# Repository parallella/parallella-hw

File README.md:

PARALLELLA: Supercomputing for Everyone
========================================	

This repository contains open source board and FPGA designs associated with the Parallella project. 

## Directory

Board                                | Description                | CAD       | Status     |
-------------------------------------|----------------------------|-----------|------------|
[parallella](parallella/README.md)   | Parallella                 | Cadence   | Production |
[porcupine](porcupine/README.md)     | Parallella Breakout Board  | KiCad     | Production |
[meta](meta)                         | Epiphany 4096-core System  | Cadence   | Prototype  |
[buddy](buddy)                       | Epiphany-V Evaluation Board| Cadence   | Prototype  |
[paracase](paracase)                 | Aluminum Case              | SolidWorks| Production |
[parasdr](parasdr/README.md)         | SDR adapter Board          | Cadence   | Production |
[kvision](kvision/README.md)         | Stereo Vision Board        | Altium    | Prototype  |
[paralime](paralime)                 | Myriad-RF daughter Board   | KiCad     | Prototype  |
[paracluster](paracluster/README.md) | Cluster Board              | N/A       | Prototype  |
[paralib](paralib)                   | CAD librares               | Various   | Prouction  |
[paratemplate](paratemplate)         | Daugher Card Template      | KiCad     | Production |
[paratile](paratile/README.md)       | Breakout Board             | Eagle     | Prototype  |
[aafm](aafm/README.md)               | Epiphany-III FMC Board     | KiCad     | Production |
[archive](archive)                   | Old Parallella stuff       | N/A       | Obsolete   |

## FPGA Design Sources
All Parallella related FPGA sources have been moved to the [OH! library](https://github.com/parallella/oh) library and released under MIT license.

## License
Board design files are released under the Creative Common Share Alike license unlesss otherwise specified.

## How to do a pull-request

1. Fork this repository to your personal github account using the 'fork' button 2. above
3. Clone your 'parallella-hw' fork to a local computer using 'git clone'
4. Create a new sub-directory at the root of the repo
5. Add your project files with the appropriate license clearly stated
6. Add a README.md file (see the skeleton directory for a template)
7. Use git add-->git commit-->git push to add changes to your fork of 'parallella-examples'
8. Submit a pull request by clicking the 'pull request' button on YOUR github 'parallella-examples' repo.

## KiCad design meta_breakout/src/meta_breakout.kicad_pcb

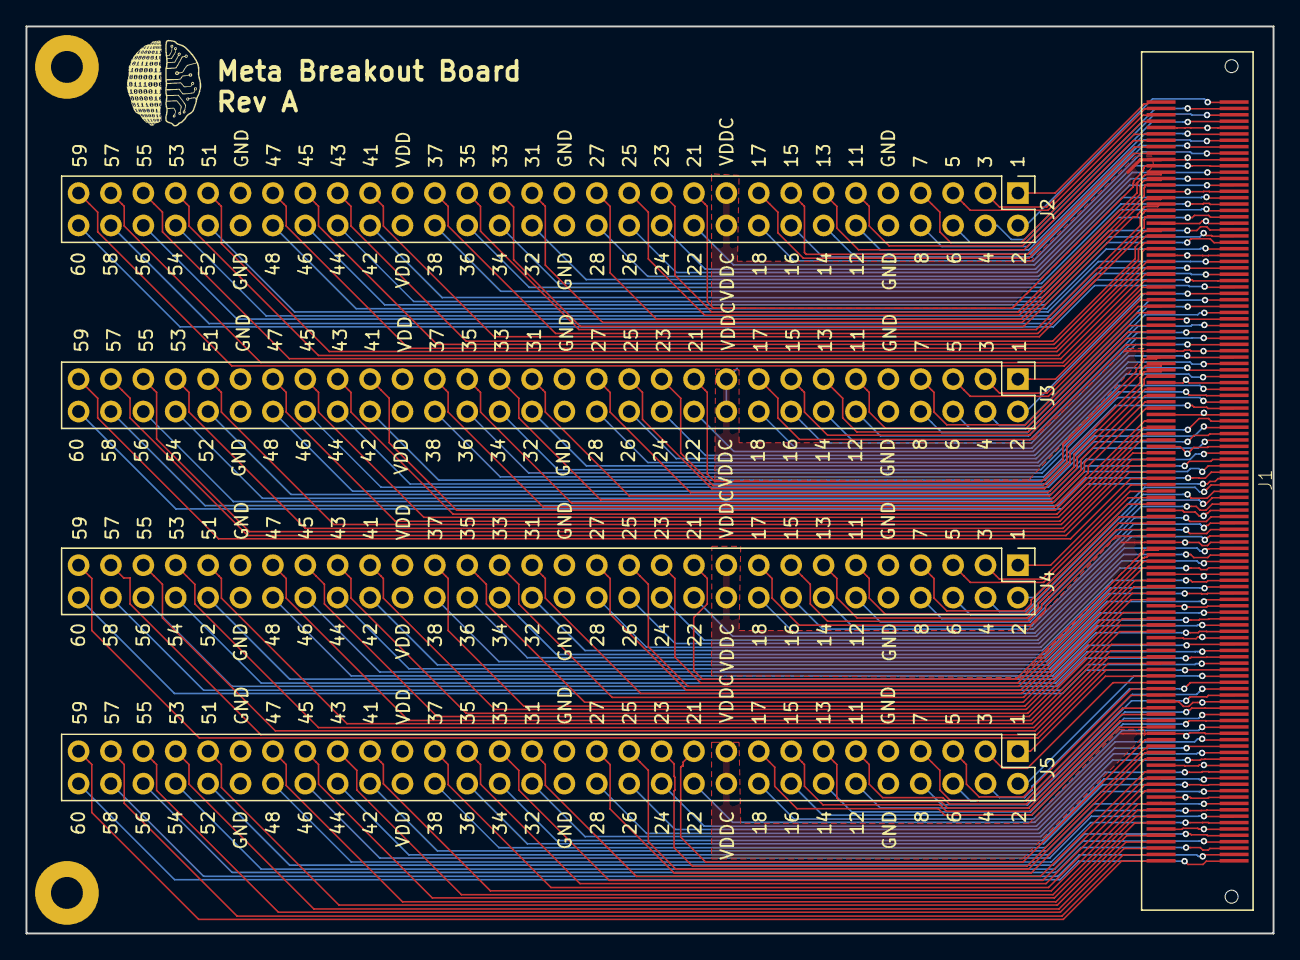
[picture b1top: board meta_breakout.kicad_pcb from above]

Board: 4 copper layers, 97.8 x 71.1 mm, 5 parts (0 on the bottom side), 209 nets.

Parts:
J1: BSH-120; BSH-120-01-X-D-A
J2, J3, J4, J5: Conn_02x30_Odd_Even; PinHeader_2x30_P2.54mm_Vertical

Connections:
/CTRL_IN0: J1.59, J2.59
/CTRL_IN1: J1.119, J3.59
/CTRL_IN2: J1.179, J4.59
/CTRL_IN3: J1.239, J5.59
/CTRL_OUT0: J1.60, J2.60
/CTRL_OUT1: J1.120, J3.60
/CTRL_OUT2: J1.180, J4.60
/CTRL_OUT3: J1.240, J5.60
/DATA_IN_N0: J1.21, J2.21
/DATA_IN_N1: J1.25, J2.25
/DATA_IN_N2: J1.31, J2.31
/DATA_IN_N3: J1.35, J2.35
/DATA_IN_N4: J1.41, J2.41
/DATA_IN_N5: J1.45, J2.45
/DATA_IN_N6: J1.51, J2.51
/DATA_IN_N7: J1.55, J2.55
/DATA_IN_N8: J1.81, J3.21
/DATA_IN_N9: J1.85, J3.25
/DATA_IN_N10: J1.91, J3.31
/DATA_IN_N11: J1.95, J3.35
/DATA_IN_N12: J1.101, J3.41
/DATA_IN_N13: J1.105, J3.45
/DATA_IN_N14: J1.111, J3.51
/DATA_IN_N15: J1.115, J3.55
/DATA_IN_N16: J1.141, J4.21
/DATA_IN_N17: J1.145, J4.25
/DATA_IN_N18: J1.151, J4.31
/DATA_IN_N19: J1.155, J4.35
/DATA_IN_N20: J1.161, J4.41
/DATA_IN_N21: J1.165, J4.45
/DATA_IN_N22: J1.171, J4.51
/DATA_IN_N23: J1.175, J4.55
/DATA_IN_N24: J1.201, J5.21
/DATA_IN_N25: J1.205, J5.25
/DATA_IN_N26: J1.211, J5.31
/DATA_IN_N27: J1.215, J5.35
/DATA_IN_N28: J1.221, J5.41
/DATA_IN_N29: J1.225, J5.45
/DATA_IN_N30: J1.231, J5.51
/DATA_IN_N31: J1.235, J5.55
/DATA_IN_P0: J1.23, J2.23
/DATA_IN_P1: J1.27, J2.27
/DATA_IN_P2: J1.33, J2.33
/DATA_IN_P3: J1.37, J2.37
/DATA_IN_P4: J1.43, J2.43
/DATA_IN_P5: J1.47, J2.47
/DATA_IN_P6: J1.53, J2.53
/DATA_IN_P7: J1.57, J2.57
/DATA_IN_P8: J1.83, J3.23
/DATA_IN_P9: J1.87, J3.27
/DATA_IN_P10: J1.93, J3.33
/DATA_IN_P11: J1.97, J3.37
/DATA_IN_P12: J1.103, J3.43
/DATA_IN_P13: J1.107, J3.47
/DATA_IN_P14: J1.113, J3.53
/DATA_IN_P15: J1.117, J3.57
/DATA_IN_P16: J1.143, J4.23
/DATA_IN_P17: J1.147, J4.27
/DATA_IN_P18: J1.153, J4.33
/DATA_IN_P19: J1.157, J4.37
/DATA_IN_P20: J1.163, J4.43
/DATA_IN_P21: J1.167, J4.47
/DATA_IN_P22: J1.173, J4.53
/DATA_IN_P23: J1.177, J4.57
/DATA_IN_P24: J1.203, J5.23
/DATA_IN_P25: J1.207, J5.27
/DATA_IN_P26: J1.213, J5.33
/DATA_IN_P27: J1.217, J5.37
/DATA_IN_P28: J1.223, J5.43
/DATA_IN_P29: J1.227, J5.47
/DATA_IN_P30: J1.233, J5.53
/DATA_IN_P31: J1.237, J5.57
/DATA_OUT_N0: J1.22, J2.22
/DATA_OUT_N1: J1.26, J2.26
/DATA_OUT_N2: J1.32, J2.32
/DATA_OUT_N3: J1.36, J2.36
/DATA_OUT_N4: J1.42, J2.42
/DATA_OUT_N5: J1.46, J2.46
/DATA_OUT_N6: J1.52, J2.52
/DATA_OUT_N7: J1.56, J2.56
/DATA_OUT_N8: J1.82, J3.22
/DATA_OUT_N9: J1.86, J3.26
/DATA_OUT_N10: J1.92, J3.32
/DATA_OUT_N11: J1.96, J3.36
/DATA_OUT_N12: J1.102, J3.42
/DATA_OUT_N13: J1.106, J3.46
/DATA_OUT_N14: J1.112, J3.52
/DATA_OUT_N15: J1.116, J3.56
/DATA_OUT_N16: J1.142, J4.22
/DATA_OUT_N17: J1.146, J4.26
/DATA_OUT_N18: J1.152, J4.32
/DATA_OUT_N19: J1.156, J4.36
/DATA_OUT_N20: J1.162, J4.42
/DATA_OUT_N21: J1.166, J4.46
/DATA_OUT_N22: J1.172, J4.52
/DATA_OUT_N23: J1.176, J4.56
/DATA_OUT_N24: J1.202, J5.22
/DATA_OUT_N25: J1.206, J5.26
/DATA_OUT_N26: J1.212, J5.32
/DATA_OUT_N27: J1.216, J5.36
/DATA_OUT_N28: J1.222, J5.42
/DATA_OUT_N29: J1.226, J5.46
/DATA_OUT_N30: J1.232, J5.52
/DATA_OUT_N31: J1.236, J5.56
/DATA_OUT_P0: J1.24, J2.24
/DATA_OUT_P1: J1.28, J2.28
/DATA_OUT_P2: J1.34, J2.34
/DATA_OUT_P3: J1.38, J2.38
/DATA_OUT_P4: J1.44, J2.44
/DATA_OUT_P5: J1.48, J2.48
/DATA_OUT_P6: J1.54, J2.54
/DATA_OUT_P7: J1.58, J2.58
/DATA_OUT_P8: J1.84, J3.24
/DATA_OUT_P9: J1.88, J3.28
/DATA_OUT_P10: J1.94, J3.34
/DATA_OUT_P11: J1.98, J3.38
/DATA_OUT_P12: J1.104, J3.44
/DATA_OUT_P13: J1.108, J3.48
/DATA_OUT_P14: J1.114, J3.54
/DATA_OUT_P15: J1.118, J3.58
/DATA_OUT_P16: J1.144, J4.24
/DATA_OUT_P17: J1.148, J4.28
/DATA_OUT_P18: J1.154, J4.34
/DATA_OUT_P19: J1.158, J4.38
/DATA_OUT_P20: J1.164, J4.44
/DATA_OUT_P21: J1.168, J4.48
/DATA_OUT_P22: J1.174, J4.54
/DATA_OUT_P23: J1.178, J4.58
/DATA_OUT_P24: J1.204, J5.24
/DATA_OUT_P25: J1.208, J5.28
/DATA_OUT_P26: J1.214, J5.34
/DATA_OUT_P27: J1.218, J5.38
/DATA_OUT_P28: J1.224, J5.44
/DATA_OUT_P29: J1.228, J5.48
/DATA_OUT_P30: J1.234, J5.54
/DATA_OUT_P31: J1.238, J5.58
/FRAME_IN_N0: J1.5, J2.5
/FRAME_IN_N1: J1.65, J3.5
/FRAME_IN_N2: J1.125, J4.5
/FRAME_IN_N3: J1.185, J5.5
/FRAME_IN_P0: J1.7, J2.7
/FRAME_IN_P1: J1.67, J3.7
/FRAME_IN_P2: J1.127, J4.7
/FRAME_IN_P3: J1.187, J5.7
/FRAME_OUT_N0: J1.6, J2.6
/FRAME_OUT_N1: J1.66, J3.6
/FRAME_OUT_N2: J1.126, J4.6
/FRAME_OUT_N3: J1.186, J5.6
/FRAME_OUT_P0: J1.8, J2.8
/FRAME_OUT_P1: J1.68, J3.8
/FRAME_OUT_P2: J1.128, J4.8
/FRAME_OUT_P3: J1.188, J5.8
/GND: J1.9, J1.10, J1.29, J1.30, J1.49, J1.50, J1.69, J1.70, J1.89, J1.90, J1.109, J1.110, J1.129, J1.130, J1.149, J1.150, J1.169, J1.170, J1.189, J1.190, J1.209, J1.210, J1.229, J1.230, J2.9, J2.10, J2.29, J2.30, J2.49, J2.50, J3.9, J3.10, J3.29, J3.30, J3.49, J3.50, J4.9, J4.10, J4.29, J4.30, J4.49, J4.50, J5.9, J5.10, J5.29, J5.30, J5.49, J5.50
/LCLK_IN_N0: J1.1, J2.1
/LCLK_IN_N1: J1.61, J3.1
/LCLK_IN_N2: J1.121, J4.1
/LCLK_IN_N3: J1.181, J5.1
/LCLK_IN_P0: J1.3, J2.3
/LCLK_IN_P1: J1.63, J3.3
/LCLK_IN_P2: J1.123, J4.3
/LCLK_IN_P3: J1.183, J5.3
/LCLK_OUT_N0: J1.2, J2.2
/LCLK_OUT_N1: J1.62, J3.2
/LCLK_OUT_N2: J1.122, J4.2
/LCLK_OUT_N3: J1.182, J5.2
/LCLK_OUT_P0: J1.4, J2.4
/LCLK_OUT_P1: J1.64, J3.4
/LCLK_OUT_P2: J1.124, J4.4
/LCLK_OUT_P3: J1.184, J5.4
/VDD0: J1.19, J1.20, J2.19, J2.20
/VDD1: J1.79, J1.80, J3.19, J3.20
/VDD2: J1.139, J1.140, J4.19, J4.20
/VDD3: J1.199, J1.200, J5.19, J5.20
/VDDIO0: J1.39, J1.40, J2.39, J2.40
/VDDIO1: J1.99, J1.100, J3.39, J3.40
/VDDIO2: J1.159, J1.160, J4.39, J4.40
/VDDIO3: J1.219, J1.220, J5.39, J5.40
/WAIT_RD_IN_N0: J1.16, J2.16
/WAIT_RD_IN_N1: J1.76, J3.16
/WAIT_RD_IN_N2: J1.136, J4.16
/WAIT_RD_IN_N3: J1.196, J5.16
/WAIT_RD_IN_P0: J1.18, J2.18
/WAIT_RD_IN_P1: J1.78, J3.18
/WAIT_RD_IN_P2: J1.138, J4.18
/WAIT_RD_IN_P3: J1.198, J5.18
/WAIT_RD_OUT_N0: J1.15, J2.15
/WAIT_RD_OUT_N1: J1.75, J3.15
/WAIT_RD_OUT_N2: J1.135, J4.15
/WAIT_RD_OUT_N3: J1.195, J5.15
/WAIT_RD_OUT_P0: J1.17, J2.17
/WAIT_RD_OUT_P1: J1.77, J3.17
/WAIT_RD_OUT_P2: J1.137, J4.17
/WAIT_RD_OUT_P3: J1.197, J5.17
/WAIT_WR_IN_N0: J1.12, J2.12
/WAIT_WR_IN_N1: J1.72, J3.12
/WAIT_WR_IN_N2: J1.132, J4.12
/WAIT_WR_IN_N3: J1.192, J5.12
/WAIT_WR_IN_P0: J1.14, J2.14
/WAIT_WR_IN_P1: J1.74, J3.14
/WAIT_WR_IN_P2: J1.134, J4.14
/WAIT_WR_IN_P3: J1.194, J5.14
/WAIT_WR_OUT_N0: J1.11, J2.11
/WAIT_WR_OUT_N1: J1.71, J3.11
/WAIT_WR_OUT_N2: J1.131, J4.11
/WAIT_WR_OUT_N3: J1.191, J5.11
/WAIT_WR_OUT_P0: J1.13, J2.13
/WAIT_WR_OUT_P1: J1.73, J3.13
/WAIT_WR_OUT_P2: J1.133, J4.13
/WAIT_WR_OUT_P3: J1.193, J5.13

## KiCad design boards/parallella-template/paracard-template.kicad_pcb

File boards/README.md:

# Parallella Boards

This section contains all PCB-related info, including schematics, pcb layouts, and libraries.
FPGA pin constraints are also included for each board with an FPGA.

## Projects

```
archive              - Old boards, for reference
paracard-template    - KiCad template for Parallella Daughtercards
parallella-I         - Current Parallella
parallella-porcupine - Connector breakout board for Parallella
```

## Templates

To install the paracard-template onto your system, copy the entire directory to your KiCad
template directory, keeping the name the same.  KiCad will pick this up the next time it is
started.  On my Linux system it's under _~/kicad/template/_.  Or for the more adventurous,
drop it into the the system templates: Windows PC directory _C:\Program Files\KiCad\share\template_,
or on Linux under _/usr/local/share/kicad/template_, although
the application seemed to be looking for it under _/usr/local/share/template_ and I haven't
found where to change that path.  In the meantime I added a link from where it's looking 
to where it is.

If you don't want to do that, you can simply open the project where it sits, and save it to
another project as you like.  In any case you may have to re-set the library paths for your system.

## Libraries

I recommend the [kicadlibrarian utility](http://www.compuphase.com/electronics/kicadlibrarian_en.htm)
to help managing the libraries.  I was not able to get the package from Slavco's repository to install on my Ubuntu 13.10 x86-64 laptop, but it built easily from source.

## Notes about 3D models

I found [this guide](http://happyrobotlabs.com/posts/tutorials/tutorial-3d-kicad-parts-using-openscad-and-wings3d/)
helpful.

It recommends creating the models in [OpenSCAD](http://www.openscad.org/), which is 
a great 3D scripting language.  It's easy to see how models can be parameterized to re-use 
one source for many similar parts.  There is a [user manual here](http://en.wikibooks.org/wiki/OpenSCAD_User_Manual).

Note that OpenSCAD claims their units are millimiters, but by the time the model got to 
KiCad it came out off by a factor of 0.3937, apparently Wings3D uses units of 0.1", bizarre. 
This is easily repaired either in the source model by doing a final translation to units of 0.1" 
(as I've done with conn_samtec_bth_60), or in KiCad's model editor.  The model is rendered 
and exported as STL, too bad OpenSCAD doesn't speak VRML which is a very similar script-like 
format that looks quite similar to OpenSCAD's.

The STL model then needs to be translated to binary (apparently) or it won't import into 
Wings3D, which is done with [meshconv from here](http://www.cs.princeton.edu/~min/meshconv/).
The tool also claims to be removing a pile of duplicate faces, not sure if Wings was having
trouble with that or just the ascii-binary issue.

```
meshconv -c stl model.stl -o model.conv.stl
```

And finally [Wings3D](http://www.wings3d.com/) is used to convert the STL model to VRML and 
optionally add color to the model.

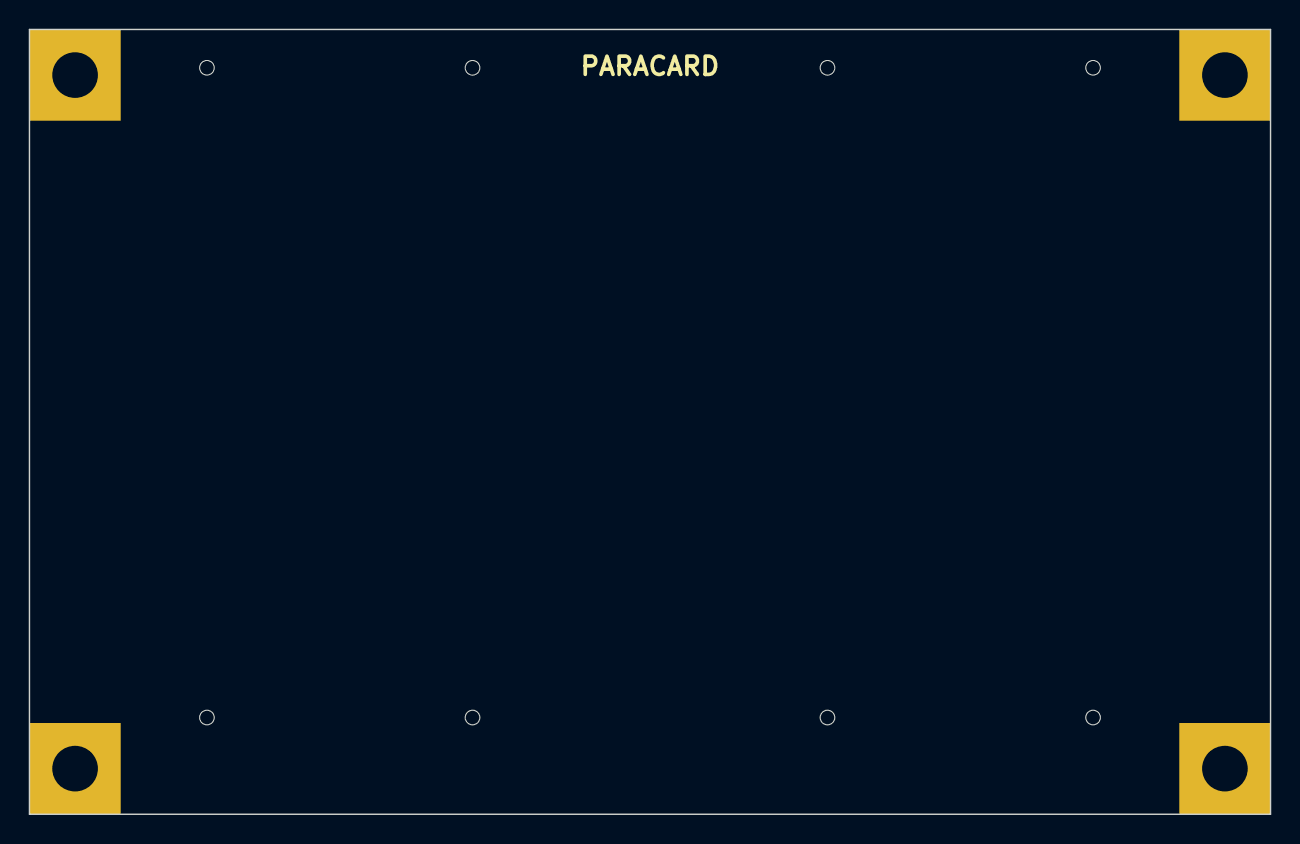
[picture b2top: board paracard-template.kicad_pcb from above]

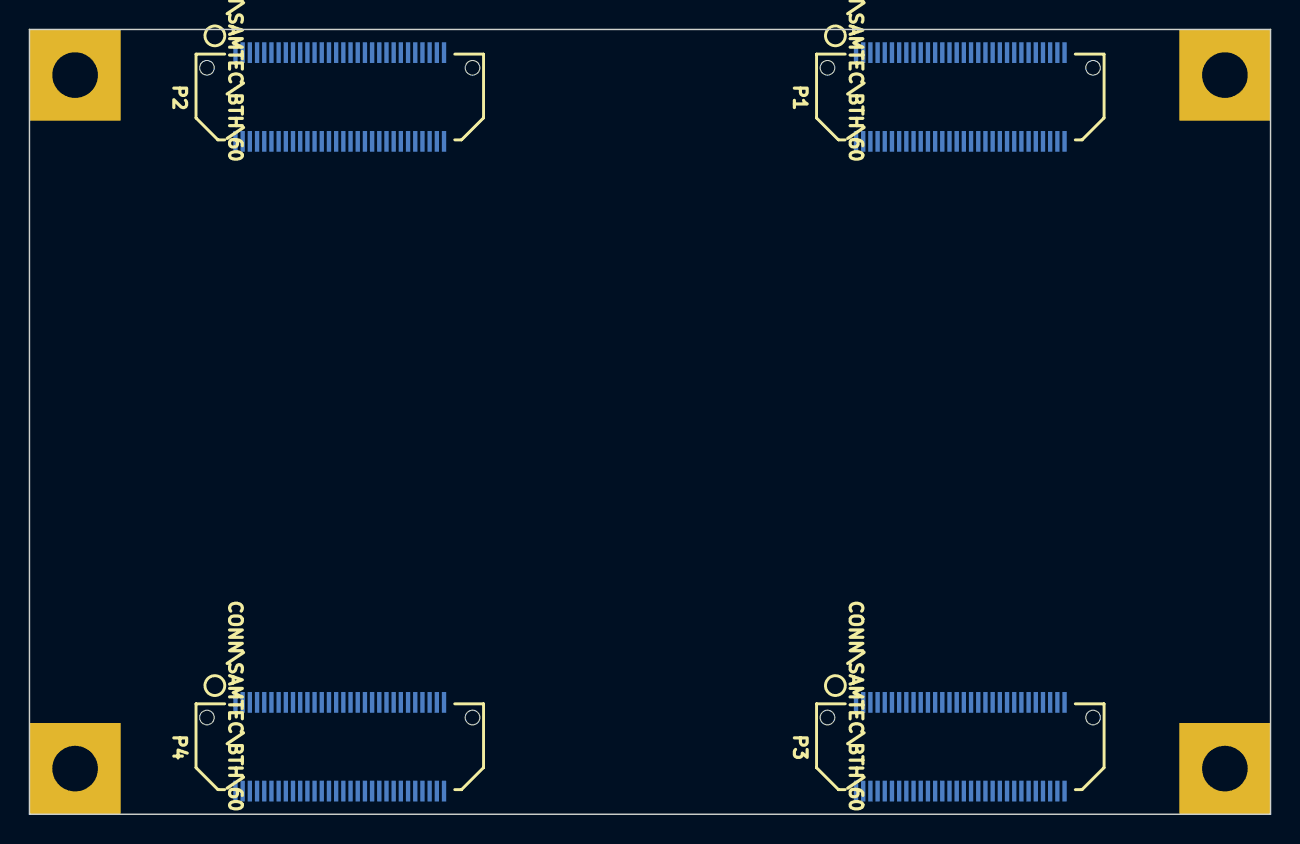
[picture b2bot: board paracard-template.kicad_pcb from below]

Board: 2 copper layers, 86.4 x 54.6 mm, 8 parts (4 on the bottom side), 14 nets, no tracks yet.

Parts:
MH1, MH2, MH3, MH4: MTG\PTH\125\SQ; MTG_PTH_125_SQ
P1, P2, P3, P4: CONN\SAMTEC\BTH\60; CONN_SAMTEC_BTH_60

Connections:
/NORTH/VDDIO: P2.1, P2.2
/POWER/1P0V: P3.43, P3.44
/POWER/1P8V: P3.49, P3.50
/POWER/1P35V: P3.47, P3.48
/POWER/2P5V: P3.57, P3.58
/POWER/3P3V: P3.59, P3.60
/POWER/SYS_5P0V: P3.1, P3.2
/POWER/VDD_ADJ: P3.53, P3.54
/POWER/VDD_DSP: P3.45, P3.46
/POWER/VDD_GPIO: P3.55, P3.56
/SOUTH/VDDIO: P4.1, P4.2
GND: MH2.1, MH3.1, MH4.1, P1.11, P1.12, P1.21, P1.22, P1.31, P1.32, P1.41, P1.42, P1.51, P1.52, P2.12, P2.22, P2.32, P2.42, P2.52, P3.11, P3.12, P3.21, P3.22, P3.31, P3.32, P3.35, P3.36, P3.41, P3.42, P3.51, P3.52, P4.12, P4.22, P4.32, P4.42, P4.52
unnamed: P2.11, P2.21, P2.31, P2.41, P2.51
unnamed: P4.11, P4.21, P4.31, P4.41, P4.51

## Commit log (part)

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2013-06-29 Initial repository creation
2013-07-03 Change schematic pdf name to avoid confusion
2013-07-11 Fixed Reg_en issue Added pull-up/down transistors on elink frame signals to avoid spurious transacftions Renamed a few pec_power signals Changed Intersil part number
2013-08-09 Changed to conforming name
2013-08-27 Added gen0 fpga design files, work in progress..
2013-08-30 Removed duplicate files (can be found in comon hdl)
2013-08-30 Removed duplicate file, added license
2013-08-30 Added .gitignore file to prepare for putting in project files
2013-08-31 HDMI support thanks to Antmicro contribution.
2013-09-23 Updated constraints file for Gen1
2013-10-10 changed RXO_RD_WAIT to single ended signal
2013-10-10 Made RXO_RD_WAIT signal single ended(removed diff buffer)
2013-11-26 Parallella "Gen1.1" Files added
2013-11-26 Removed garbage file
2014-01-24 More repository cleanup..
2014-01-24 Latest Parallella Gen1.2 changes, added safe fix for USB power issue.
2014-01-24 Updated boot images
2014-01-24 Clarification
2014-03-13 Started reorganization.
2014-03-14 Added / changed ignore rules, added runs directory to avoid errors from planAhead.
2014-03-14 Reset run data to match empty impl and synth dirs.
2014-03-19 set / clear, it's only off by 1.
2014-03-21 Cleaned-up timing issue for E64. Had to change to manual compile order for E16 project.
2014-03-26 Added 7010 project, renamed top-level file to fit w/7010 or 7020 projects, split ucf files into generic placement, 7020 extra pins, and timing. Added project-level READMEs.
2014-03-26 Markdown updates 2
2014-04-08 Updated recommended ISE version
2014-04-13 Added I2C interface to all projects, will always work for u-boot but will not be available to users unless added to device tree. Changed version register format. Removed 'k' from named defines. Added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
2014-04-18 Added ability to change elink and gpio iostandards.
2014-04-21 Mods for E64, changed version register.
2014-04-21 Bitstreams w/ new version register structure. E64 uses LVDS for eLink. No GPIOs imlemented, but there are still LVDS Rcvrs/Xmtrs on the GPIO pins (12 and 12).
2014-04-28 Minor update to readme.
2014-05-08 Changed the 'fpga/bitstreams' directory to contain board-ready binary files instead of the raw bitfile output of ISE. This is supported by new versions of 'getbits' in each project folder. Note that 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
2014-05-16 Added external repo fpgahdl_xilinx from analog devices. Added helper scripts for external repo fetch & sparse checkout.
2014-05-23 README updates.
2014-05-23 Fixed nested lists.
2014-05-23 Yeah, can't have blockquotes within an ordered list without restarting the count.
2014-06-03 Added E64 project with HDMI. Some cleanup to paracard template.
2014-06-06 First commit of porcupine board, not complete, not routed, don't use!
2014-06-17 Completed design w/3-row XID/YID and various 4-pin IO connectors. Fixed page ordering, changed "Mfr" field to "Manufacturer" Will now re-do to combine all misc. functions onto a single 2xN connector.
2014-06-19 Ready for full review.
2014-06-21 As released for fab., Rev. A.
2014-07-22 Updated flash images & readme instructions.
2014-07-28 Cleanup for Vivado project.
2014-07-29 Add create_project script, don't import PS files into project.
2014-09-02 Step #3 clarification
    Added version and flash to step 3 name to match step 9
2014-10-07 First version of new elink interface
2014-10-11 First version of new elink register file Significantly expanded feature spec: -cclk power down/divider -gpio mod -loopback support -start of irq/mmu feature -traffic monitor
2014-11-03 Adding some memory wrappers (not yet tested)
2014-11-03 Adding a monitor block for elink -tracks wait signals -tracks access signals (not verified)
2014-11-04 Adding a simple dv unit test for configuration file
2014-11-04 Removing interrupt signal
2014-11-05 Adding module for testing the monitor circuit
2014-11-05 Adding generic memory modules -insert tecnology specific macros insides (BRAM etc)
2014-11-05 Lint fix (matching bit widths)
2014-11-06 Run script for embox
2014-11-06 Changed to 20 bit addressing for clarity in FPGA
2014-11-06 Adding run.sh files for simulation
2014-11-06 Adding readback indicator for AXI slave mux
2014-11-06 Basic interfaces..still need to add the axi signals and fill in the content
2014-11-06 Adding place holders for hard macros
2014-11-06 More file organization Adding some more utility functions
2014-11-06 Deleting old files (moved to src)
2014-11-19 Added elink-gold -> elink2 test project.
2014-11-24 Minor fixes for implementation.
2014-12-12 Removing old files not needed by new design
2014-12-12 Changed module name for new structure
2014-12-14 Incremental renaming
2014-12-14 Adding new verilog modules for receiver and transmitter -moving away from Vivado block editor -creating a "clean" split between RX and TX
2014-12-14 Adding README file describing design structure of the elink
2014-12-15 Adding fofo environment for elink to check for broken signals. Too many stub modules to be practical..next need sim models
2014-12-15 Adding stubs files for xilinx IP Goal is to create models for all of these
2014-12-15 Verious silly compilation fixes, nothing to see here..
2014-12-15 Wrong bus width (just cleanup..)
2014-12-15 Fixing port declarations (thanks Verilator!)
2015-01-28 Partial integration of new elink
2015-02-19 Porcupine Version 2.
2015-03-21 Adding the latest Vivado design archive for Parallella
2015-03-23 Includes Fred's latest bug fixes (from project archive)
2015-03-25 Massive checkin... -this may break already broken projects -creates a Verilog top level (instead of using Vivado block level design) -integrates mmy and mailbox (not completely integrated) -compiles.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
2015-04-08 Fixing bus issue with datain/dataout signal Found in Vivado... Needed to connect up the wait signals properly on dataout/datain registers
2015-04-08 Adding constants directory 1. Platform specific constants (xilinx vs altera) 2. Version specific constants Basically anything that affects `ifdefs
2015-04-09 Adding stubs for IP blocks used in elink
2015-04-09 Vivado run through -missed connections -mismatched bus widths -missing IP blocks -cleanup -proper DV starts tomorrow
2015-04-09 Removing unecessary levels of hiearchy
2015-04-09 Reorg, cleanup
2015-04-09 fixed broken links
2015-04-09 Fixing bad merge This block will be completely redesigned
2015-04-10 emmu: Refactor and add verilator testbench
    Testbench is split between the synthesizable transactors and
    non-synthesizable parts to allow reuse of transactors in the newly
    added verilator test bench
2015-04-11 Reorganizing files...too many folders after all. There is only one elink...
2015-04-12 Changing emesh/elink transaction order Our "standard packet" order should be followed everywhere to ease verification and integration (standards are good fir reuse...): [0]=access [1]=write [3:2]=dat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
2015-04-14 Clean up of old files
2015-04-14 Adding missing stubs
2015-04-14 Added "fufu" DV environment for elink -Icarus for now, verilator comes next -Using our "standard" emesh interface ..here we go...
2015-04-14 Verilator lint cleanup ~10 real bugs -mostly name mismatches and bit range mistakes
2015-04-15 Adding back the "common" directory
2015-04-15 Running with "TARGET_CLEAN"
2015-04-15 Adding platform agnostic dual ported memory and async fifo
2015-04-15 Continued work to create clean design: -pll bypass for clocks (customer request) -adding dividers on all clocks (tx/cclk) -adding reset block (clearer) -using commong clock_divider block -need to cle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
2015-04-15 Fixing startup issues in transmit path: -adding reset signals to synchronizer to solve startup issues -setting config in test bench for speedup, default reg config now correct -fix (my) stupid bug in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
2015-04-15 Xilinx models -adding ODDR model -configuring the ecfg (rx/tx/clk) in testbench
2015-04-16 Renaming to something more clear (per user input...)
2015-04-17 Changing ESYSCLK definition (again.....) old implementation felt too "cutsy" this makes for a cleaner usage model (simple shift with param) also splitting out enable but, not making the CTIMER mistak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
2015-04-17 Fixed odd/even copy past bug on DDR sampler
2015-04-17 MILESTONE: Open souce simulation elink loopback working!
2015-04-18 Adding documentation to elink top level module
2015-04-18 Spell checking comments First time ever using spell cheker in EMACS. Hard to believe...but it's true! I am sure this speaks volume for how little I have commented my code over the years!
2015-04-18 Prettifying format..starting to look decent
2015-04-18 Adding high level single ported memory
2015-04-18 Clock divider fixup -changed to latest and hopefully final register config -fixed functional bugs (was broken..) -added xor for sensing change of clock frequency
2015-04-18 Removed synchronizer on TXLCLK
2015-04-18 Changed register map -Moved "groups" to E,D,C -Changed names to EL* (shorter is better, clear enough) -Moved order to fit logical operation during init -Moved embox registers to MMR group DONE!
2015-04-18 Clock cleanup -Adding enable signal to clock out. Definitely right decision to keep separate bit from the divider field. -Fixed settings for to fit new register field -XILINX version is still broken!!
2015-04-18 Adding gtkwave signals file
2015-04-20 MMU working... -Needs more testing
2015-04-21 Adding emesh memory module (empty for now)
2015-04-21 Wrong port direction on output
2015-04-21 Rename
2015-04-21 Added wait signal for reads
2015-04-21 Adding test for readback from host
2015-05-23 Add ESDK 2015.1 compatible bitstreams
    These are the ones used in Pubuntu 2015.1
2015-06-24 Adding smaller logo
2015-06-24 Added logo
2016-02-03 Adding PCI-104 Parallella board -Work in progress, more news later -Comments appreciated!
2016-02-03 Adding incomplete parallella-rf board -Uses AD9361 -Started by Fred Huettig
2016-02-03 Consolidating the community hw repo
2016-02-04 Adding PR instructions
2016-02-04 Restoring README file
2016-02-04 Fixed errors..sigh
2016-02-04 Adding status field -Important to show status to built trust
2016-03-01 Adding datasheets folder for convenience
2016-04-11 Copyright transfer - Assigning license to the non-profit Parallella Foundation
2016-04-27 Adding bringup pictures for kvision (from Emil)
2016-05-20 Adding README for porcupine
2016-05-20 Adding README and explicit license for porcupine
2016-05-20 Cleanup top README links
2016-05-20 Adding lime rf board
2016-08-26 Cleaning up meta/4k specs
2016-09-23 Adding AAFM Epiphany FMC board to repository
2016-10-14 Adding meta pinout file
2016-10-21 Updating pinout for meta -Need separate height connector for control
2016-11-23 Adding porcupine product shots
2016-11-23 Adding gerbers
2016-11-23 Adding physical case picture
2016-12-28 Adding Porcupine pinout diagram -Git tired of having to look through schematics...
2016-12-28 fix type in readme
2016-12-28 Fixing typo on south connector diagram (thanks Twitter!)
2016-12-30 Reorg of sdr project
2017-01-08 Cleaning up olad files
2017-01-08 Formatting again...
2017-01-08 Contributing the buddy open source evaluation board
2017-05-18 Fix BOM for meta module - remove resistors as appropriate to set coordinates - DNP for certain features
2017-05-18 Adding pick and place for parasdr
2017-06-10 Fixing BOM. Wrong samtec connector was omitted !!!!!
2017-07-09 Fixed BOM for E5 buddy board
2017-08-06 Reviewing BOM. Fixing 4 parts errors. You have got to be fu*king kidding me!!!!
2017-09-30 Adding schematics
2017-10-01 Splitting module and carrier for meta -Separate boards -Cleaner split, more consistent
2017-10-01 Cleanup old files
2018-01-27 Adding more dataseet references
2018-04-23 Fixes to various meta board issues -oscillator value -5V rail resistor changes -Added FMC connector -DNPs for throug-holes (mechanical clearance issues) -fixed voltage ratings on capacitors for 12V r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
2018-06-11 Adding a KiCad symbols library for Samtec connector
